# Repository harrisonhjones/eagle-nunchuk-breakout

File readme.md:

# Nunchuk Breakout
A breakout board for the Wii Nunchuk

## Version History

| Revision # | Schematic | Board | BOM | Top | Bottom |  Purchase Link | Notes |
| ---- | ---- | ---- | ---- | ---- | ---- | ---- | ---- |
| 0 | N/A | N/A | N/A | N/A | N/A | N/A | Initial Version. No locking mechanism. Produced on a PCB mill @ college. Works |
| 1 | N/A | N/A | N/A | N/A | N/A | N/A | New version with locking mechanism and built to straddle a solderless breakout board |
| 2 | N/A | N/A | N/A | N/A | N/A | N/A | Similar to Rev 1. Now contains alignment square to help show which way the Nunchuck should be plugged in |
| 3 | N/A | N/A | N/A | N/A | N/A | N/A | Added `enable` pin for enabling/disabling the nunchuck so multiple can be used |
| 4 | [SCH](source/Rev4.sch), [PDF](schematics/Rev4.sch.pdf) | [BRD](source/Rev4.brd), [PDF](boards/Rev4.brd.pdf) | N/A | [PNG](renderings/Rev4.top.png) | [PNG](renderings/Rev4.bot.png) | [OSHPark ($2.00 for 3)](https://oshpark.com/projects/nHR9gFSK) | Added hopefully stronger locking section. |
| 5 | [SCH](source/Rev5.sch), [PDF](schematics/Rev5.sch.pdf) | [BRD](source/Rev5.brd), [PDF](boards/Rev5.brd.pdf) | N/A | N/A | N/A | N/A | Added frame on schematic. Moved date to better location. Added open-hardware logo |
| 6 | [SCH](source/Rev6.sch), [PDF](schematics/Rev6.sch.pdf) | [BRD](source/Rev6.brd), [PDF](boards/Rev6.brd.pdf) | N/A | [PNG](renderings/Rev6.top.png) | [PNG](renderings/Rev6.bot.png) | [OSHPark ($2.55 for 3)](https://oshpark.com/projects/g8WnvhAW) | Extended the nunchuk male connector so it clears when on a breadboard |

## To Do

* Rename all versions of `Nunchuck` with 'proper' spelling `nunchuk`

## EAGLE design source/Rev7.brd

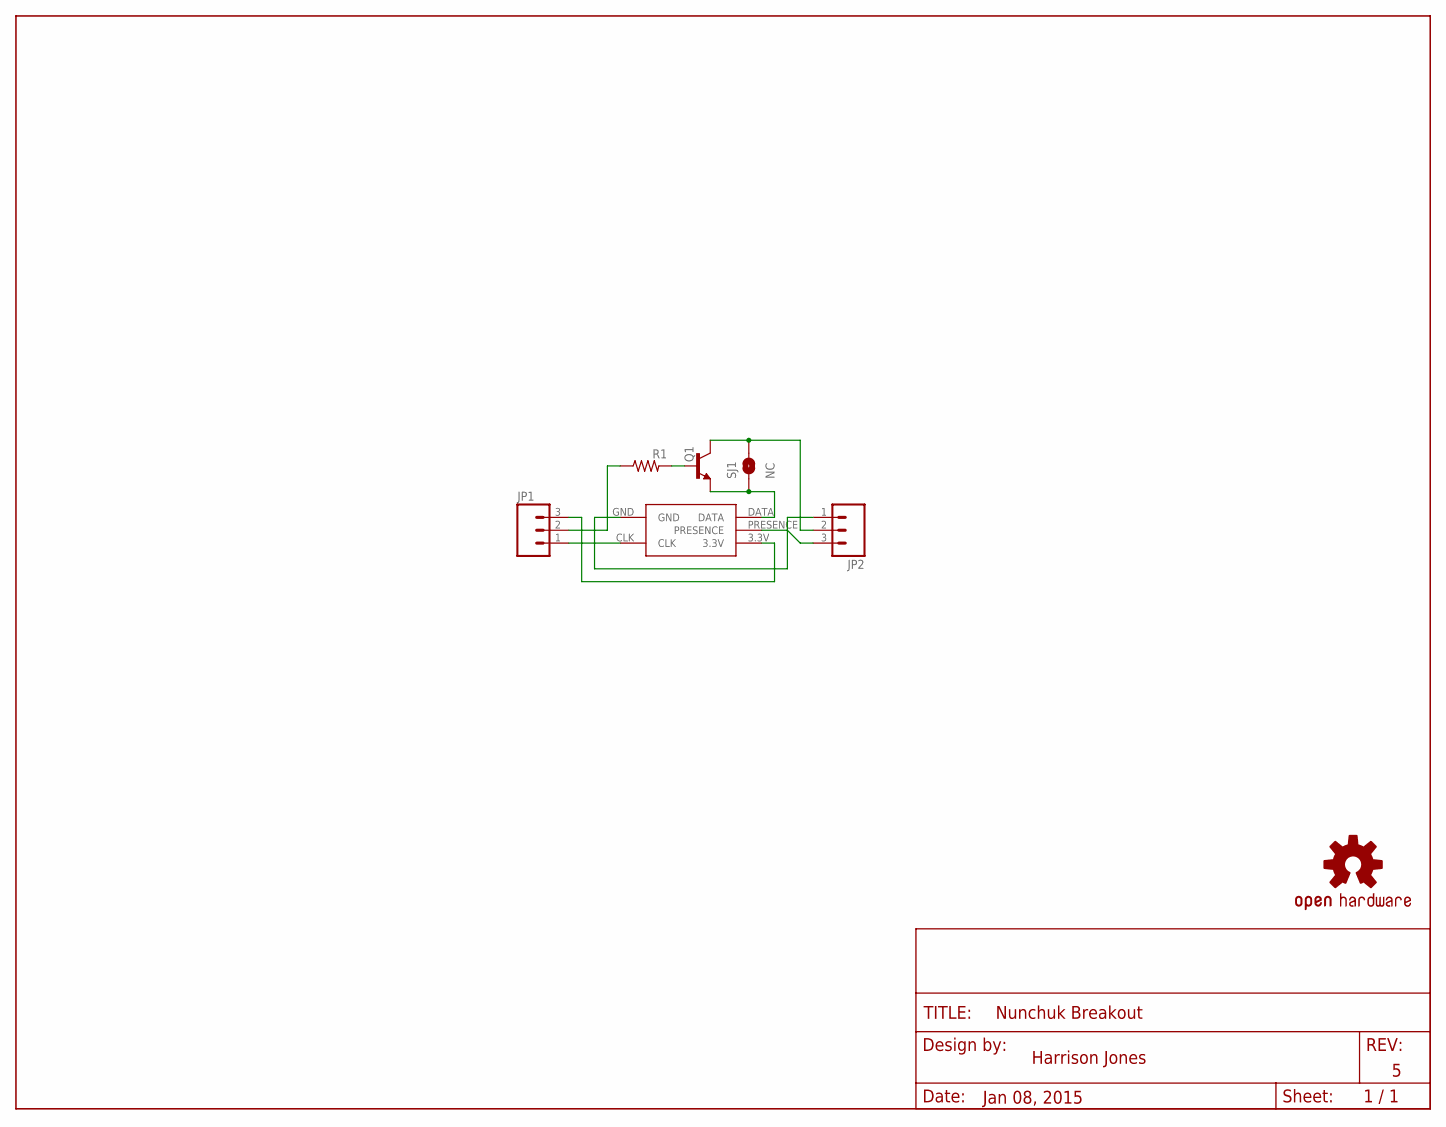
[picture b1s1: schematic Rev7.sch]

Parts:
JP1, JP2: M03PTH; 1X03
LOGO1: OSHW-LOGOS; OSHW-LOGO-S
Q1: TRANSISTOR_NPNSOT23; SOT23
R1: RESISTOR0603; 0603-RES
SJ1: NC; SJ_2S-TRACE
U$1: NUNCHUCKLOCL; NUNCHUCK-LOCK
U$2: DOC_FIELD

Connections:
3.3V: JP1.3, U$1.3.3V
EN: JP1.2, R1.1
GND: JP2.1, U$1.GND
unnamed: Q1.1 (B), R1.2
unnamed: JP2.3, U$1.PRESENCE
unnamed: JP2.2, Q1.3 (C), SJ1.2
SCL: JP1.1, U$1.CLK
SDA: Q1.2 (E), SJ1.1, U$1.DATA

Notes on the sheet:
Nunchuk Breakout
Harrison Jones
Jan 08, 2015
1 / 1

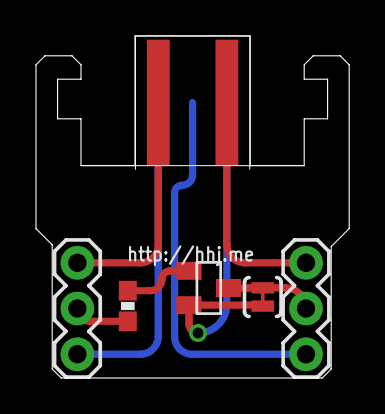
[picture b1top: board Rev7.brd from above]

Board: 2 copper layers, 17.4 x 19.0 mm, 8 parts (1 on the bottom side), 8 nets.

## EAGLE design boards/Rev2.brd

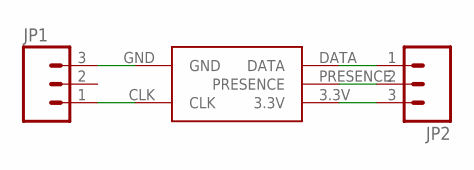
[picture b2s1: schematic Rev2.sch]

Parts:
JP1, JP2: M03PTH; 1X03
U$1: NUNCHUCKLOCL; NUNCHUCK-LOCK

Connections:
3.3V: JP2.3, U$1.3.3V
CLK: JP1.1, U$1.CLK
DATA: JP2.1, U$1.DATA
GND: JP1.3, U$1.GND
PRESENCE: JP2.2, U$1.PRESENCE

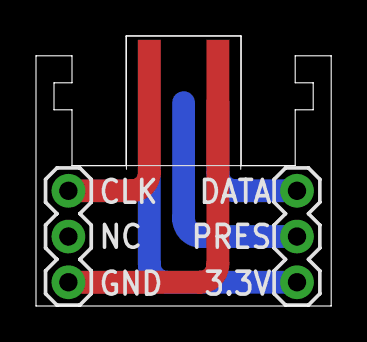
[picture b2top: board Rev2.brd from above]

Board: 2 copper layers, 16.4 x 15.0 mm, 3 parts (0 on the bottom side), 5 nets.

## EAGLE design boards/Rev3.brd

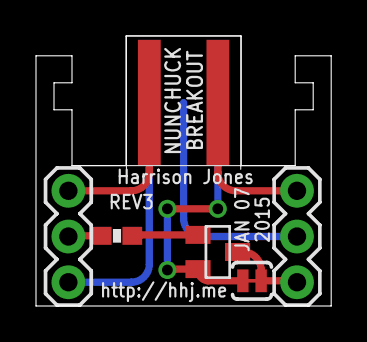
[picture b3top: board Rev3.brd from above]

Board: 2 copper layers, 16.4 x 15.0 mm, 6 parts (0 on the bottom side), 8 nets.

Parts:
JP1, JP2: 1X03
Q2: SOT23
R2: 0603-RES
SJ1: SOLDERJUMPERTRACE; SJ_2S-TRACE
U$1: NUNCHUCKLOCL; NUNCHUCK-LOCK

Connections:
3.3V: JP1.3, U$1.3.3V
EN: JP1.2, R2.1
GND: JP2.1, U$1.GND
unnamed: Q2.1, R2.2
unnamed: JP2.3, Q2.3, SJ1.2
PRES: JP2.2, U$1.PRESENCE
SCL: JP1.1, U$1.CLK
SDA: Q2.2, SJ1.1, U$1.DATA

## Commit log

2015-01-08 Basic readme
2015-01-08 Changed filetree structure
2015-01-08 Eagle wants source files in same folder
2015-01-08 Updated to reflect file tree
2015-01-08 Ignoring gerbers
2015-01-08 Updated misspelled name
2015-01-08 Minor table formatting fix
2015-01-08 See readme.md for updates
2015-03-07 added Rev 6. Board change for better breadboard compatibility
2015-03-08 Working on Rev 7. Changed layer colors and moved vias around for better text placement
2015-03-08 Updated Rev7: down to 1 via and much better signal layout. Pin layout has changed

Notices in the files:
parts and their libraries:
SparkFun-Connectors: Licensing: CC v3.0 Share-Alike You are welcome to use this library for commercial purposes.
